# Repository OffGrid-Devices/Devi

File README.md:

# Devi
Arduino-based synthesizer 

[BOM](https://docs.google.com/spreadsheets/d/11OAxCDL9WJjP-PPryWPdmoXp5gGi14y3Fq-VU7GaQAA/edit?usp=sharing)

# Notes for further development

## Synth Variables

- fixedfreq (bool)
- coarse 
- detune 
- freqrange
- freqfixed
- depth 
- waveform
- attack
- decay 
- algorithm 

## Main Functions

- handleNoteOn
- handleNoteOff
- handleCC
- handleProgramChange
- sendNoteOn
- sendNoteOff
- sendCC
- sendProgramChange
- setMIDICH // runs @setup()
- setProgChangeBehavior // runs @setup()
- savePreset
- loadPreset
- initParams
- updateParams // hardware version of handleCC

## Control Modes

### 0 - Volumes & Mod Depths (RGB=OFF)
- knobs => depth 
- buttons do nothing (or may play individual oscillators)
- LED's show which oscillators are carriers

### 1 - Frequency (RGB=PURPLE)
- button + function => select if oscillator as fixed frequency or not (indicate with LED)
- knob => detune/freqfixed
- button + knob => coarse/freqrange

### 2 - Envelopes (RGB=BLUE)
- button + knob => attack
- knob => decay

### 3 - Waveform (RGB=WHITE)
- knob => waveform  
- buttons + knob6 => set several 
- function + knob => set all

### 4 - Load Preset (RGB=GREEN)
(leds indicate which preset is loaded using a binary representation)
### 5 - Save Preset (RGB=RED)

## FM Algorithms

### 0: six-voice polyphony, single oscillator
(1)|(2)|(3)|(4)|(5)|(6) 

### 1: three-voice polyphony, dual oscillator
(1)+(2)|(3)+(4)|(5)+(6)

### 2: two-voice polyphony, triple oscillator
(1)+(2)+(3)|(4)+(5)+(6)

### 3: three-voice polyphony, FM 2-operators
(2) | (4) | (6)
 |  |  |  |  |
(1) | (3) | (5)

### 4: two-voice polyphony, FM 3-operators
    (2) |     (6)
     |  |      | 
(1)+(3) | (4)+(5)

### 5: two-voice polyphony, FM 3-operators
  (3)   |   (6)
  / \   |   / \
(1)+(2) | (4)+(5)

### 6: two-voice polyphony, FM 3-operators
(2)+(3) | (5)+(6) 
  \ /   |   \ / 
  (1)   |   (4)

### 7: two-voice polyphony, FM 3-operators
(3) | (6)
 |  |  |
(2) | (5)
 |  |  |
(1) | (4)

### 8: monophonic, FM 6-operators
(3) (6)
 |   |
(2) (5)
 |   |
(1)+(4)

### 9: monophonic, FM 6-operators
  (3)     (6)
  / \     / \
(1)+(2) (4)+(5)

### 10: monophonic, FM 6-operators (needs experimentation...is it worth it have 6 stacked oscils when it is possible to change the waveform?)
    (6)             (6)
     |               |
    (5)             (5)
     |       OR      |
(2) (4)             (4)
 |   |               |
(1)+(3)             (3)
                     |
                    (2)
                     |
                    (1) 

### 11: super monophonic, six oscillators
(1)+(2)+(3)+(4)+(5)+(6)

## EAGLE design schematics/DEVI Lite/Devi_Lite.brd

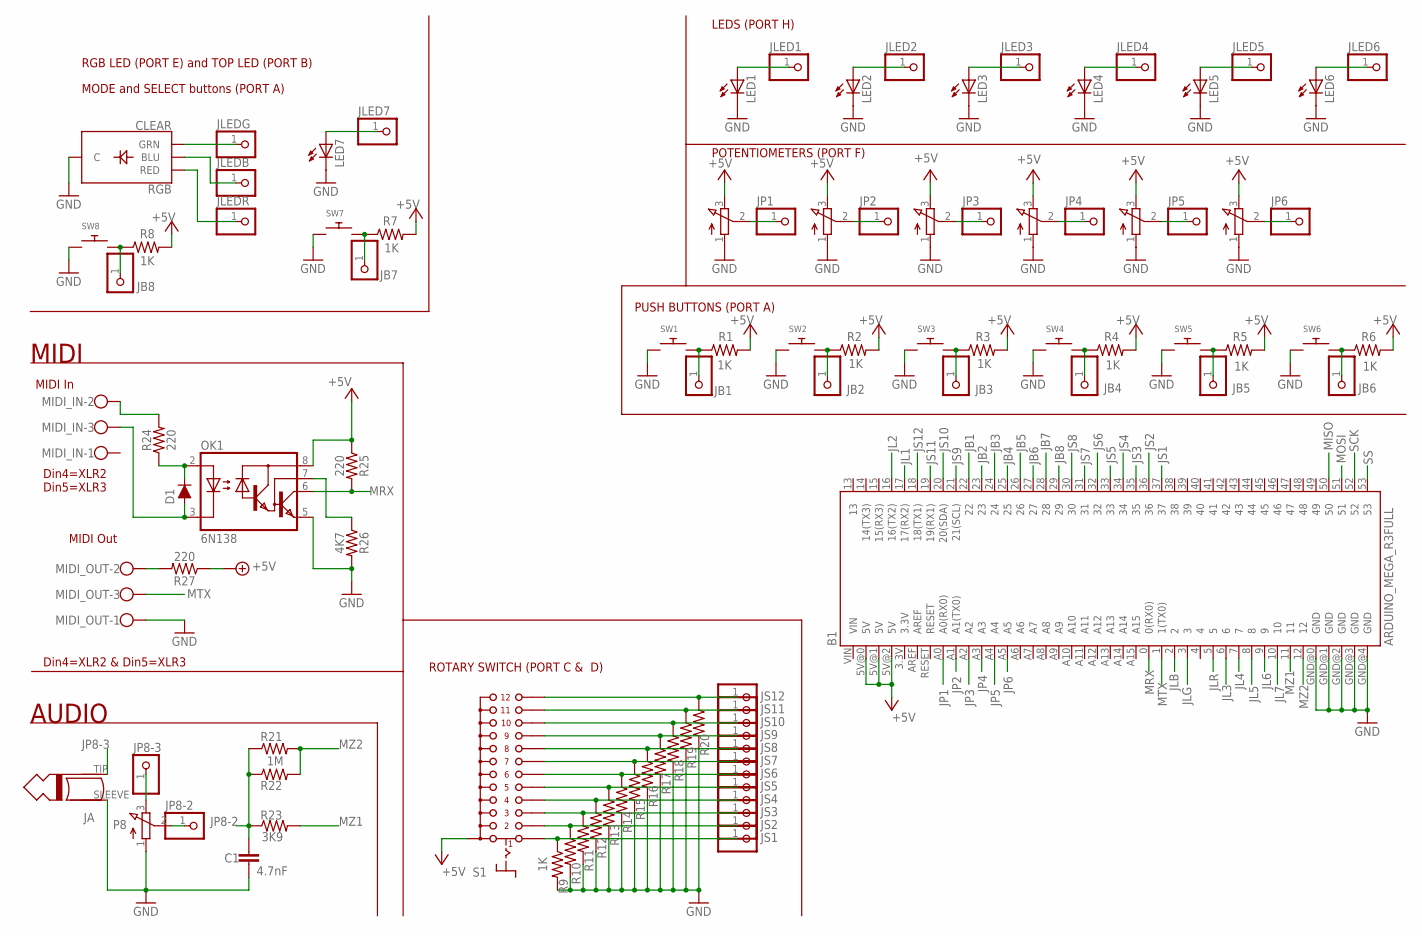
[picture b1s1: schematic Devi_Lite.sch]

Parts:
B1: ARDUINO_MEGA_R3FULL; ARDUINO_MEGA
C1: 4.7nF; C050-025X075
D1: 200mA/100V/1V; DIODE-1N4148
JA: MONO_PLUG; TWO_PADS
JB1, JB2, JB3, JB4, JB5, JB6, JB7, JB8: PINHD-1X1CB; 1X01-CLEANBIG
JLED1, JLED2, JLED3, JLED4, JLED5, JLED6, JLED7: PINHD-1X1CB; 1X01-CLEANBIG
JLEDB: PINHD-1X1CB; 1X01-CLEANBIG
JLEDG: PINHD-1X1CB; 1X01-CLEANBIG
JLEDR: PINHD-1X1CB; 1X01-CLEANBIG
JP1, JP2, JP3, JP4, JP5, JP6, JP8-2, JP8-3: PINHD-1X1CB; 1X01-CLEANBIG
JS1, JS2, JS3, JS4, JS5, JS6, JS7, JS8, JS9, JS10, JS11, JS12: PINHD-1X1CB; 1X01-CLEANBIG
LED1, LED2, LED3, LED4, LED5, LED6, LED7: LED3MM
MIDI_IN: W237-103
MIDI_OUT: W237-103
OK1: 6N138; DIL08
P1, P2, P3, P4, P5, P6, P8: 3RP/1610N
R1, R2, R3, R4, R5, R6, R7, R8, R9, R10, R11, R12, R13, R14, R15, R16, R17, R18, R19, R20: 1K; AXIAL-0.3
R21, R22: 1M; AXIAL-0.3
R23: 3K9; AXIAL-0.3
R24, R25, R27: 220; AXIAL-0.3
R26: 4K7; AXIAL-0.3
RGB: CLEAR; LED-RGB-THRU
S1: CK101X12
SW1, SW2, SW3, SW4, SW5, SW6, SW7, SW8: SWITCH_PUSHBUTTONEVQ-PE; TACT_PANA-EVQ

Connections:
+5V: B1.5V@0 (5V), B1.5V@1 (5V), B1.5V@2 (5V), OK1.8 (VCC), P1.3 (E), P2.3 (E), P3.3 (E), P4.3 (E), P5.3 (E), P6.3 (E), R1.P$2 (2), R2.P$2 (2), R3.P$2 (2), R4.P$2 (2), R5.P$2 (2), R6.P$2 (2), R7.P$2 (2), R8.P$2 (2), R25.P$1 (1), R27.P$1 (1), S1.A
GND: B1.GND@0 (GND), B1.GND@1 (GND), B1.GND@2 (GND), B1.GND@3 (GND), B1.GND@4 (GND), C1.2, JA.SLEEVE, LED1.K (C), LED2.K (C), LED3.K (C), LED4.K (C), LED5.K (C), LED6.K (C), LED7.K (C), MIDI_OUT.1, OK1.5 (GND), P1.1 (A), P2.1 (A), P3.1 (A), P4.1 (A), P5.1 (A), P6.1 (A), P8.1 (A), R9.P$2 (2), R10.P$2 (2), R11.P$2 (2), R12.P$2 (2), R13.P$2 (2), R14.P$2 (2), R15.P$2 (2), R16.P$2 (2), R17.P$2 (2), R18.P$2 (2), R19.P$2 (2), R20.P$2 (2), R26.P$2 (2), RGB.2 (C), SW1.P$1, SW2.P$1, SW3.P$1, SW4.P$1, SW5.P$1, SW6.P$1, SW7.P$1, SW8.P$1
JB1: B1.22, JB1.1, R1.P$1 (1), SW1.P$2
JB2: B1.23, JB2.1, R2.P$1 (1), SW2.P$2
JB3: B1.24, JB3.1, R3.P$1 (1), SW3.P$2
JB4: B1.25, JB4.1, R4.P$1 (1), SW4.P$2
JB5: B1.26, JB5.1, R5.P$1 (1), SW5.P$2
JB6: B1.27, JB6.1, R6.P$1 (1), SW6.P$2
JB7: B1.28, JB7.1, R7.P$1 (1), SW7.P$2
JB8: B1.29, JB8.1, R8.P$1 (1), SW8.P$2
JL1: B1.17 (17(RX2)), JLED1.1, LED1.A
JL2: B1.16 (16(TX2)), JLED2.1, LED2.A
JL3: B1.6, JLED3.1, LED3.A
JL4: B1.7, JLED4.1, LED4.A
JL5: B1.8, JLED5.1, LED5.A
JL6: B1.9, JLED6.1, LED6.A
JL7: B1.10, JLED7.1, LED7.A
JLB: B1.2, JLEDB.1, RGB.4 (BLU)
JLG: B1.3, JLEDG.1, RGB.3 (GRN)
JLR: B1.5, JLEDR.1, RGB.1 (RED)
JP1: B1.A0 (A0(RX0)), JP1.1, P1.2 (S)
JP2: B1.A1 (A1(TX0)), JP2.1, P2.2 (S)
JP3: B1.A2, JP3.1, P3.2 (S)
JP4: B1.A3, JP4.1, P4.2 (S)
JP5: B1.A4, JP5.1, P5.2 (S)
JP6: B1.A5, JP6.1, P6.2 (S)
JP8-2: C1.1, JP8-2.1, P8.2 (S), R21.P$1 (1), R22.P$1 (1), R23.P$1 (1)
JP8-3: JA.TIP, JP8-3.1, P8.3 (E)
JS1: B1.37, JS1.1, R9.P$1 (1), S1.1
JS2: B1.36, JS2.1, R10.P$1 (1), S1.2
JS3: B1.35, JS3.1, R11.P$1 (1), S1.3
JS4: B1.34, JS4.1, R12.P$1 (1), S1.4
JS5: B1.33, JS5.1, R13.P$1 (1), S1.5
JS6: B1.32, JS6.1, R14.P$1 (1), S1.6
JS7: B1.31, JS7.1, R15.P$1 (1), S1.7
JS8: B1.30, JS8.1, R16.P$1 (1), S1.8
JS9: B1.21 (21(SCL)), JS9.1, R17.P$1 (1), S1.9
JS10: B1.20 (20(SDA)), JS10.1, R18.P$1 (1), S1.10
JS11: B1.19 (19(RX1)), JS11.1, R19.P$1 (1), S1.11
JS12: B1.18 (18(TX1)), JS12.1, R20.P$1 (1), S1.12
MISO: B1.50
MOSI: B1.51
MRX: B1.0 (0(RX0)), OK1.6 (VO), R25.P$2 (2)
MTX: B1.1 (1(TX0)), MIDI_OUT.3
MZ1: B1.11, R23.P$2 (2)
MZ2: B1.12, R21.P$2 (2), R22.P$2 (2)
unnamed: D1.A, MIDI_IN.3, OK1.3 (C)
unnamed: D1.C, OK1.2 (A), R24.P$1 (1)
unnamed: MIDI_IN.2, R24.P$2 (2)
unnamed: OK1.7 (VB), R26.P$1 (1)
unnamed: MIDI_OUT.2, R27.P$2 (2)
SCK: B1.52
SS: B1.53

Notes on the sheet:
POTENTIOMETERS (PORT F)
PUSH BUTTONS (PORT A)
RGB LED (PORT E) and TOP LED (PORT B)
LEDS (PORT H)
MODE and SELECT buttons (PORT A)
MIDI
MIDI In
Din4=XLR2 Din5=XLR3
MIDI Out
Din4=XLR2 & Din5=XLR3
ROTARY SWITCH (PORT C & D)
AUDIO

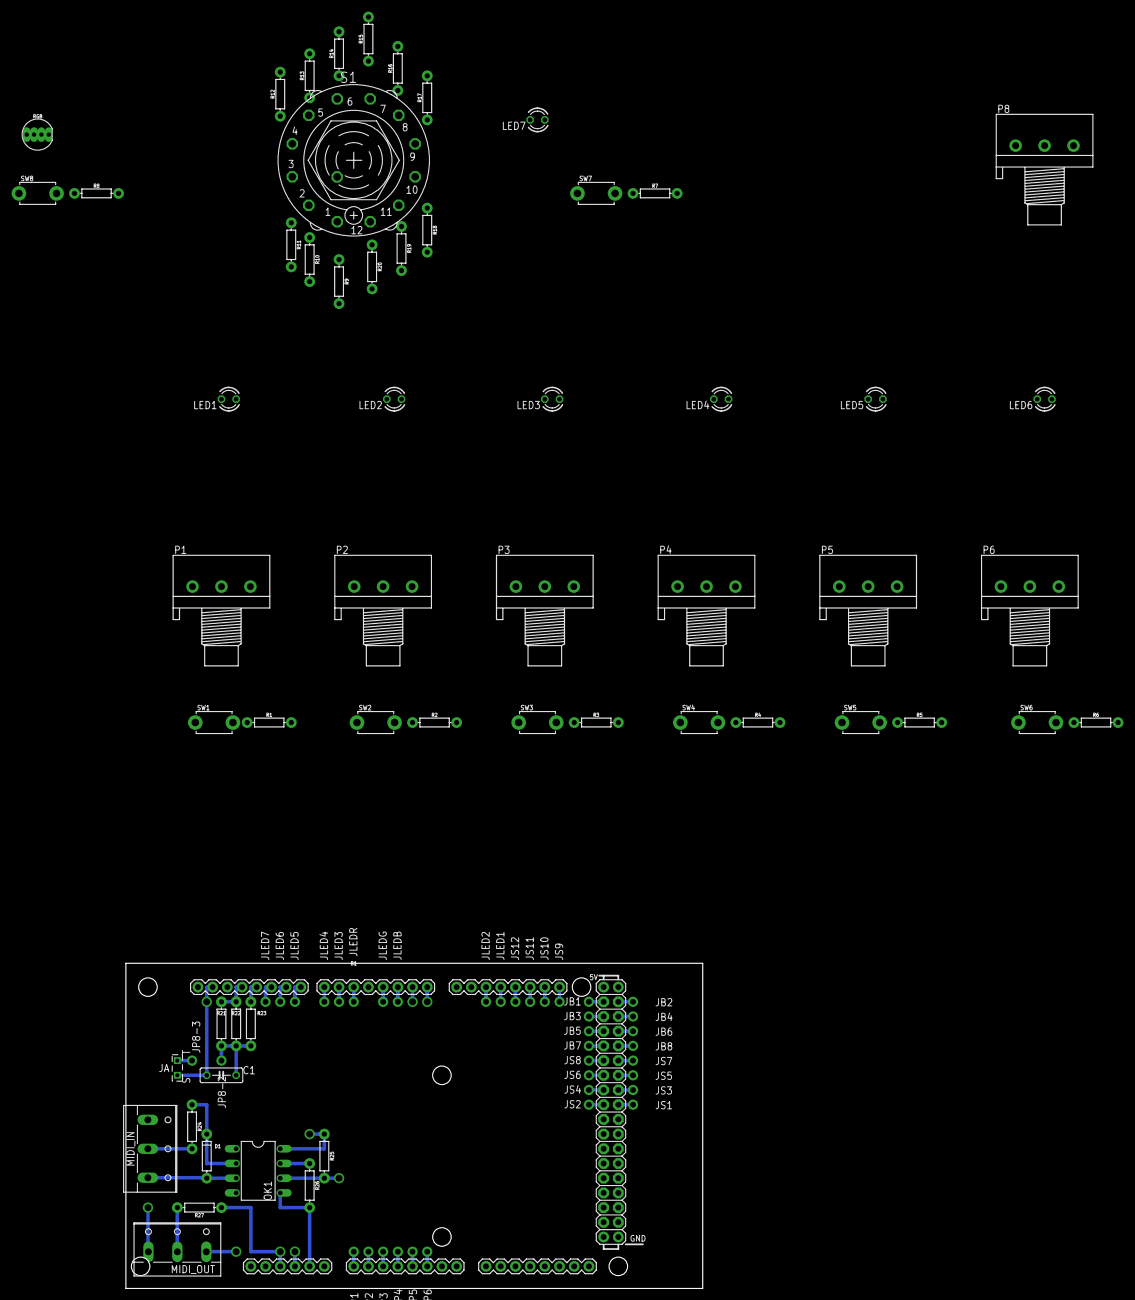
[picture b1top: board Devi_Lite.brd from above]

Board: 16 copper layers, 99.7 x 56.2 mm, 96 parts (0 on the bottom side), 49 nets.

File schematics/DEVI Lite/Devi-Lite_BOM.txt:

Partlist exported from C:/Users/tiago/Documents/GitHub/OffGrid-Devices/Devi/schematics/DEVI Lite/Devi_Lite.sch at 22-05-2018 23:34

Qty Value               Device                  Package       Parts                                                                                                                                                                                                                   Description                     
7                       3RP/1610N               3RP/1610N     P1, P2, P3, P4, P5, P6, P8                                                                                                                                                                                              16mm Potentiometer one level    
1                       CK101X12                CK101X12      S1                                                                                                                                                                                                                      ROTARY SWITCH                   
7                       LED3MM                  LED3MM        LED1, LED2, LED3, LED4, LED5, LED6, LED7                                                                                                                                                                                LED                             
38                      PINHD-1X1CB             1X01-CLEANBIG JB1, JB2, JB3, JB4, JB5, JB6, JB7, JB8, JLED1, JLED2, JLED3, JLED4, JLED5, JLED6, JLED7, JLEDB, JLEDG, JLEDR, JP1, JP2, JP3, JP4, JP5, JP6, JP8-2, JP8-3, JS1, JS2, JS3, JS4, JS5, JS6, JS7, JS8, JS9, JS10, JS11, JS12 Pin header 1x1 for 0.1" spacing 
8                       SWITCH_PUSHBUTTONEVQ-PE TACT_PANA-EVQ SW1, SW2, SW3, SW4, SW5, SW6, SW7, SW8                                                                                                                                                                                  Buttons                         
2                       W237-103                W237-103      MIDI_IN, MIDI_OUT                                                                                                                                                                                                       WAGO SCREW CLAMP                
20  1K                  1KOHM-HORIZ-1/4W-5%     AXIAL-0.3     R1, R2, R3, R4, R5, R6, R7, R8, R9, R10, R11, R12, R13, R14, R15, R16, R17, R18, R19, R20                                                                                                                               1kO resistor                    
2   1M                  1KOHM-HORIZ-1/4W-5%     AXIAL-0.3     R21, R22                                                                                                                                                                                                                1kO resistor                    
1   200mA/100V/1V       DIODE-1N4148            DIODE-1N4148  D1                                                                                                                                                                                                                      Diode                           
3   220                 1KOHM-HORIZ-1/4W-5%     AXIAL-0.3     R24, R25, R27                                                                                                                                                                                                           1kO resistor                    
1   3K9                 1KOHM-HORIZ-1/4W-5%     AXIAL-0.3     R23                                                                                                                                                                                                                     1kO resistor                    
1   4.7nF               C-EU050-025X075         C050-025X075  C1                                                                                                                                                                                                                      CAPACITOR, European symbol      
1   4K7                 1KOHM-HORIZ-1/4W-5%     AXIAL-0.3     R26                                                                                                                                                                                                                     1kO resistor                    
1   6N138               6N138                   DIL08         OK1                                                                                                                                                                                                                     MOTOROLA OPTO COUPLER           
1   ARDUINO_MEGA_R3FULL ARDUINO_MEGA_R3FULL     ARDUINO_MEGA  B1                                                                                                                                                                                                                      Arduino Mega R3                 
1   CLEAR               LED-RGB-CCCLEAR         LED-RGB-THRU  RGB                                                                                                                                                                                                                     LED-RGB Common Cathode          
1   MONO_PLUG           MONO_PLUG               TWO_PADS      JA

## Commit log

2018-04-15 uploaded hardware testers
2018-04-17 added gitignore
2018-04-17 updated gitignore
    ignore external libraries
2018-04-17 first running example
    implemented:
    - MODE button+RGB led
    - simple sequencer
2018-04-18 added pot control
    - basic potentiomer read to pitch sequence
2018-04-18 added 2nd oscillator for examplification and testing
2018-04-21 implemented mutes
2018-04-21 fixed led's not fully lit
    was forgetting to declare pins as outputs
2018-04-22 added led blinking bpm seq controls
    now stops and starts metronome according to BUTTON and MODE
2018-04-22 several improvements
    - added potentiometer class
    - cleaned code
2018-04-22 several iprovements
    - added bpm and step length control
2018-04-22 added start/stop sequence
2018-04-22 implemented sequencer modes
    up, down, up&down, palindrome, random step, random step & pitch
2018-04-22 started implementing polyphony
2018-04-22 changed mozzi version to master(22-04-2018)
    the stable release was making glitches when summing all 6 oscillators
    for polyphony
2018-04-22 minor changes
2018-04-22 added compiler optimization define in GLOBALS
2018-04-23 implemented ADSR but left Ead
2018-05-22 Devi schematics
2018-05-22 Devi_Lite schematics
2018-05-22 added veroboard size
2018-05-22 updated pin numbers
2018-05-22 changed gitignore
2018-05-22 add Devi-Lite BOM
2018-05-22 schematic for MIDI Din to minijack cable
2018-05-23 removed old comment
2018-05-23 added port comment
2018-05-25 updated gitignore
2018-05-25 gitignore minor change
2018-05-25 hardware changes
2018-05-25 Starting Devi-Lite firmware
2018-05-25 added header file for global variables
2018-05-25 minor doxygen correction
2018-05-25 reading buttons via PIN
2018-05-25 Added compiler optimization flag
2018-05-25 implemented rotary switch read
2018-05-25 Implemented Mode button+led
2018-05-25 devised Sketch skeleton
2018-05-25 working version with minor ui control bugs
    still implementing mode and function locks
2018-05-25 fixed start/stop sequencer control
2018-05-25 Step mutes working
    although there is stil a minor glitch in the muted led's (no biggie for
    now)
2018-05-25 WORKING VERSION
2018-05-25 Code refactor
2018-05-25 Sequencer is now able to run on all mode
    If stopped in Sequencer Mode it won't run on other modes
2018-05-25 minor fix and cleanup
2018-05-25 added EEPROM library
2018-05-25 added rotary switch read function
2018-05-25 defined preset variables in a struct
2018-05-25 Cleaning Voice
    NOTE: some clicks started to appear after the last changes (preset
    struct)
2018-05-25 Changed CONTROL_RATE
    changing the control rate to 256 removed glitches caused by preset
    struct
2018-05-25 added wavetables
2018-05-25 refactored and declared Voice functions
2018-05-25 declared functions
2018-05-26 implemented setCarrierWave()
2018-05-26 implemented editorA: carrier pitch and waveform
2018-05-26 implemented editorB and D
    mod amount and envelope to mod amount and envelope attack/decay
2018-05-26 uploaded Devi-Lite pdf schematics
2018-05-27 latest
2018-05-27 uploaded arduino-formatted code
2019-01-09 minor
2019-01-09 clean up
2019-01-14 added example
2019-01-14 basic functioning version
    implementation of 12 FM algorithms
2019-01-18 sketch version of DeviEditor application
2019-01-18 implementing midi input
    note on and note off
2019-01-18 improved FM algo calculations
    (changes in bit handling)
2019-01-18 basic polyphonic implementation
2019-01-19 FM poly 2 voices
    needs revision for efficiency in the voice update audio calcs
2019-01-19 starting anew
    proof of tech
    6 poly voices w/ attack, hold, decay and depth(aka gain)
2019-01-19 added pitch control
2019-01-19 minor improvements in detune control
2019-01-20 coarse and detune working
2019-01-20 improved updateControl calcs
    made a table for detune values instead of calculating, which would need
    divisions
2019-01-20 started to implement algorithms in updateAudio
    did not finish
2019-01-20 updated README
    included stuff to do with some guidelines
2019-01-20 minor changes
    added a temp solution to solve MIDI bug

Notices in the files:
parts and their libraries:
SparkFun-DiscreteSemi: Licensing: Creative Commons ShareAlike 4.0 International - https://creativecommons.org/licenses/by-sa/4.0
